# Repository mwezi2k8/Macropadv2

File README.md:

# 12-key macropad 

#what is it?
this is a custom 12-key mechanical macropad i designed in kicad from scratch. it runs on a seeed studio xiao rp2040 board instead of a bulky standard dev board, which keeps the whole thing compact and cheap. it has a 4x3 switch matrix with anti-ghosting diodes, a clickable rotary encoder knob, and a 4-pin header on top for a small i2c oled display.

# why make this?
i use a 60% keyboard daily, and while it looks clean and saves desk space, losing dedicated arrow keys, media buttons, and numpad shortcuts is honestly a pain. memorizing three-key layer combos while working or gaming gets frustrating fast. 

i wanted a standalone pad with dedicated hardware buttons for stuff like discord mutes, copy-pasting, app switching, and terminal shortcuts. plus, having a physical rotary dial to control volume or scrub timelines is way more satisfying than pressing function keys.

#how does it work?
- the key matrix:* the 12 switches are wired in a 4-column by 3-row grid connected directly to the xiao gpio pins. the micro-controller quickly scans through the rows and columns to check if a circuit is closed
- diodes* each switch has its own 1n4148 diode wired in series[cite: 3]. this stops back-powering across rows so you can press multiple keys at the same time without triggering phantom ghost clicks.
- rotary encoder:* the ec11 encoder pulses signals across two data pins whenever you turn it, letting the code figure out both direction and speed for scrolling or volume adjustments. the center shaft also clicks straight down, working as a 13th input switch
- oled screen:* hooked up to 5v, ground, sda, and scl pins. it talks over the i2c bus to show what profile or layer you are on, or display real-time stats like click counters.

#hardware & pcb specs
- controller:* seeed studio xiao rp2040
- keys:* 12 push switches arranged with standard 19.05 mm (1u) spacing so normal mechanical keycaps fit properly
- diodes:* 12x 1n4148 through-hole diodes placed next to each switch
- encoder:* ec11 rotary encoder with integrated push switch
- display connector:* 4-pin 2.54mm header for 0.96" i2c oled
- board size:*85.91 mm x 84.00 mm (2-layer pcb)

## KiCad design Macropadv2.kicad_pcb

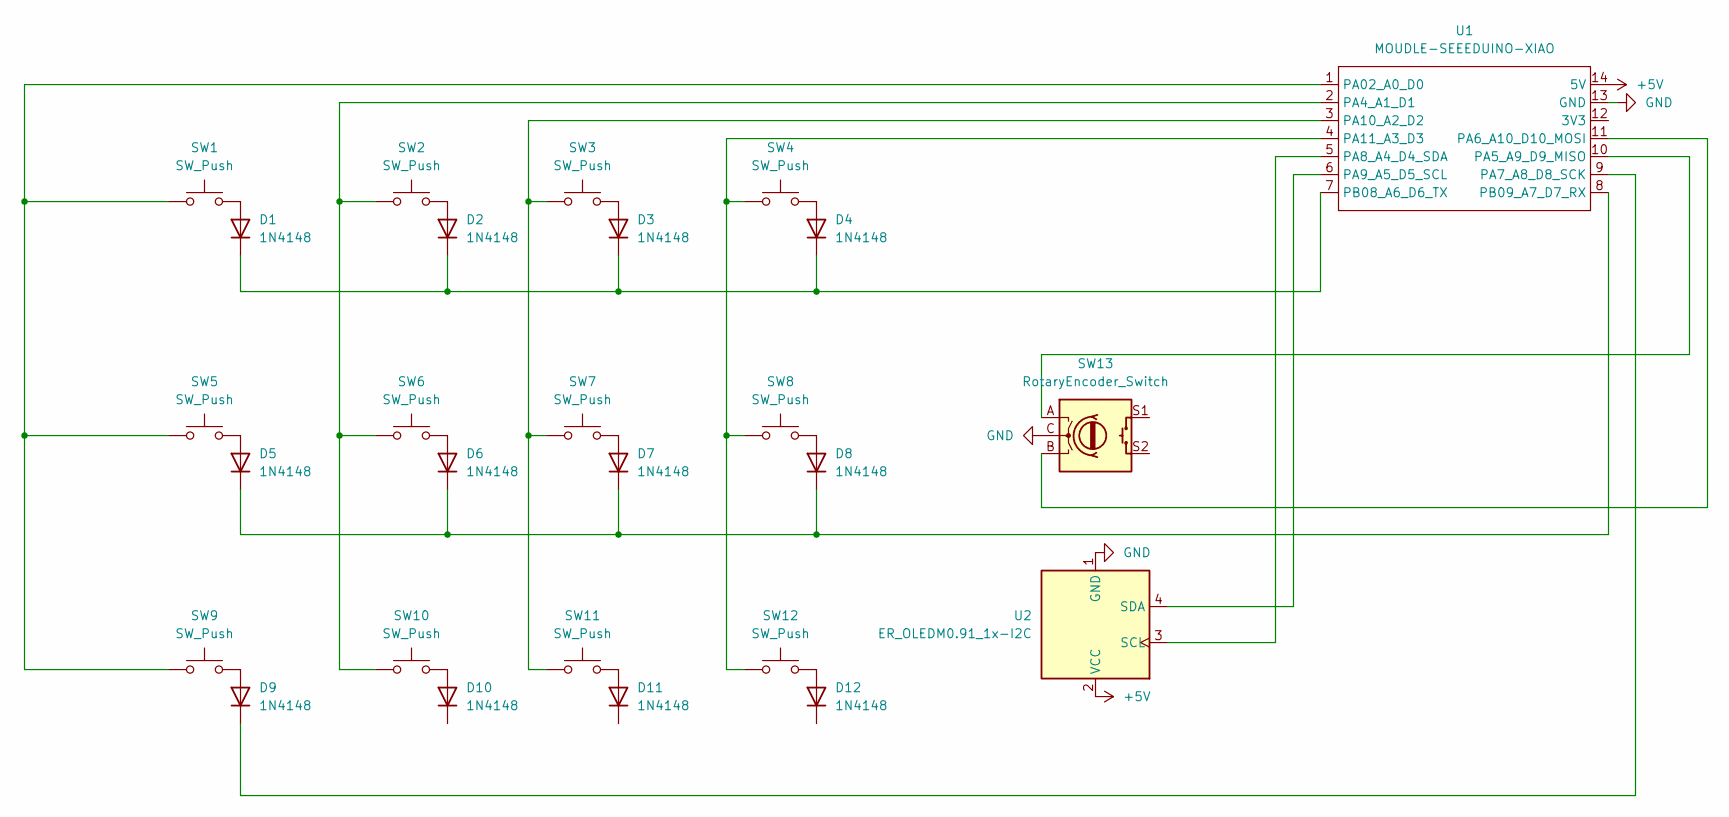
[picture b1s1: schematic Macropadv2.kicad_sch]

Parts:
D1, D2, D3, D4, D5, D6, D7, D8, D9, D10, D11, D12: 1N4148; D_DO-35_SOD27_P7.62mm_Horizontal
SW1, SW2, SW3, SW4, SW5, SW6, SW7, SW8, SW9, SW10, SW11, SW12: SW_Push; SW_NKK_GW12LJP
SW13: RotaryEncoder_Switch; RotaryEncoder_Alps_EC11E-Switch_Vertical_H20mm
U1: MOUDLE-SEEEDUINO-XIAO; XIAO-Generic-Hybrid-14P-2.54-21X17.8MM
U2: ER_OLEDM0.91_1x-I2C

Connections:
+5V: U1.14 (5V), U2.2 (VCC)
GND: SW13.C, U1.13 (GND), U2.1 (GND)
unnamed: D1.2 (A), SW1.2
unnamed: D1.1 (K), D2.1 (K), D3.1 (K), D4.1 (K), U1.7 (PB08_A6_D6_TX)
unnamed: D2.2 (A), SW2.2
unnamed: D3.2 (A), SW3.2
unnamed: D4.2 (A), SW4.2
unnamed: D5.2 (A), SW5.2
unnamed: D5.1 (K), D6.1 (K), D7.1 (K), D8.1 (K), U1.8 (PB09_A7_D7_RX)
unnamed: D6.2 (A), SW6.2
unnamed: D7.2 (A), SW7.2
unnamed: D8.2 (A), SW8.2
unnamed: D9.2 (A), SW9.2
unnamed: D9.1 (K), U1.9 (PA7_A8_D8_SCK)
unnamed: D10.2 (A_2), SW10.2
unnamed: D11.2 (A_2), SW11.2
unnamed: D12.2 (A_2), SW12.2
unnamed: SW1.1, SW5.1, SW9.1, U1.1 (PA02_A0_D0)
unnamed: SW2.1, SW6.1, SW10.1, U1.2 (PA4_A1_D1)
unnamed: SW13.A, U1.10 (PA5_A9_D9_MISO)
unnamed: SW13.B, U1.11 (PA6_A10_D10_MOSI)
unnamed: U1.5 (PA8_A4_D4_SDA), U2.3 (SCL)
unnamed: U1.6 (PA9_A5_D5_SCL), U2.4 (SDA)
unnamed: SW3.1, SW7.1, SW11.1, U1.3 (PA10_A2_D2)
unnamed: SW4.1, SW8.1, SW12.1, U1.4 (PA11_A3_D3)

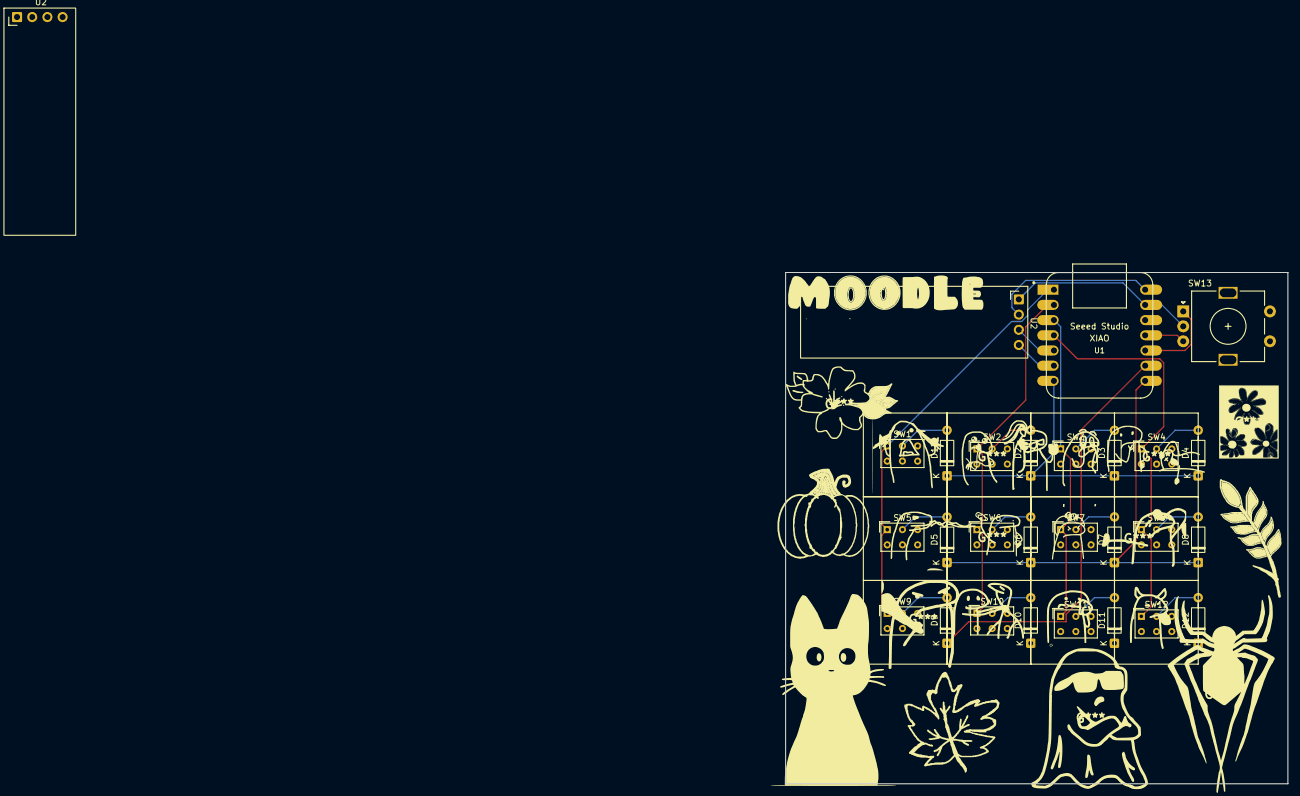
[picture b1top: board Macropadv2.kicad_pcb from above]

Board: 2 copper layers, 84.0 x 85.5 mm, 28 parts (0 on the bottom side), 25 nets.

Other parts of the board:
U2#2: ER_OLEDM0.91_1x-I2C
